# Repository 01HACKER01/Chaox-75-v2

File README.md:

# Chaox-75-v2

## what is this ??
this is a keyboard with tri mode connectivity it can be connected with the dongle(2.4gHZ), bluetooth and wired. it also charges while connected to wired 

## why it exists
i have an old evofox keyboard which is not a good keyboard i cant type fast on that keyboard sometimes the keys doesnt get clicked or sometimes teh key gets stuck so i wanted to buy a keyboard but i thought lets make one by myself so thats why i made this.

## how to assemble 
u can just place all the comps on their places on the pcb and solder them and than flash it.

## firmware stuff
this repo has the code and pcb files for my chaox-75 keyboard. i wrote the firmware in c using zephyr rtos for the nrf52840.

### what it does
* 6x15 key matrix
* works over usb (hid)
* custom fn layer with arrow keys, f-key shortcuts, and media controls

### folders
* `keyboard/` - main firmware code
* `hardware/` - pcb and schematic files
* `dongle/` - 2.4ghz dongle code
* `release/` - precompiled firmware files if u dont wanna build it urself

## how to flash
1. plug the keyboard into your pc with a usb-c cable.
2. double press the reset button on the pcb (or short the rst and gnd pins) to put it into bootloader mode. a new drive should pop up on your pc.
3. grab the `.uf2` firmware file from the releases and just drag and drop it onto that drive.
4. it will disconnect and reboot by itself in a couple seconds and ur good to go.

### what u need to build it
* nrf connect sdk 3.4.1
* zephyr rtos
* cmake & west

### status
still a work in progress (pre-release) so expect some bugs. im still working on it and will push updates when i fix things.
## issues 
it has one issue it doesnt have a switch which can change teh connectivity l;ike the dongle bluetooth or the wired thats an issue which will i fix soon.

---

Made for the CHAOX-75 project.

**CHAOX-75**  
*Custom keyboard firmware, built from the ground up.*

## BOM

| Part | Qty | Approx. USD | Link |
| -------------------------------------- | -- | ------------ | -------------------------------------------------------------------------------------------------------------------------------------------------------------- |
| Custom 82-key Keyboard PCB (5 pcs) | 1 | ~$10–25 | [JLCPCB](https://jlcpcb.com/) |
| 1.5mm Anodized Aluminum Switch Plate | 1 | ~$12–22 | [JLCPCB CNC](https://jlcpcb.com/cnc-machining) |
| 3D Printed Keyboard Case (Top & Bottom) | 1 | ~$10–20 | [JLCPCB 3D Print](https://jlcpcb.com/3d-printing) |
| MX mechanical switches (90 pcs) | 1 | ~$18–35 | [Alibaba MX switches](https://www.alibaba.com/trade/search?SearchText=mechanical+keyboard+switches+90pcs) |
| PBT keycap set (82-key / 75%) | 1 | ~$15–30 | [Alibaba PBT keycaps](https://www.alibaba.com/trade/search?SearchText=PBT+keycaps+set) |
| Kailh MX hotswap sockets (100 pcs) | 1 | ~$6–10 | [LCSC Kailh sockets](https://www.lcsc.com/search?q=kailh%20socket) |
| SK6812MINI-E reverse-mount RGB LEDs (100 pcs) | 1 | ~$8–14 | [LCSC SK6812MINI-E](https://www.lcsc.com/search?q=SK6812MINI-E) |
| 1N4148W SOD-123 diodes (100 pcs) | 1 | ~$1–2 | [LCSC 1N4148W](https://www.lcsc.com/search?q=1N4148W) |
| PCB-mount screw-in stabilizers | 1 | ~$6–12 | [Alibaba PCB stabilizers](https://www.alibaba.com/trade/search?SearchText=PCB+mount+stabilizers) |
| EC11 rotary encoder with metal knob | 1 | ~$1–2 | [LCSC EC11 encoder](https://www.lcsc.com/search?q=EC11%20encoder) |
| 0.91" 128×32 I2C OLED display | 1 | ~$1.50–3 | [LCSC 0.91 OLED](https://www.lcsc.com/search?q=0.91%20inch%20OLED%20I2C) |
| 3.7V 2500–3000mAh LiPo battery (JST-PH 2.0) | 1 | ~$5–9 | [Alibaba LiPo battery](https://www.alibaba.com/trade/search?SearchText=3.7V+3000mAh+lipo+battery+JST) |
| Poron plate foam & switch pads | 1 | ~$3–6 | [Alibaba keyboard poron foam](https://www.alibaba.com/trade/search?SearchText=poron+foam+keyboard) |
| M2 heat-set brass inserts (20 pcs) | 1 | ~$1–3 | [Alibaba M2 heat-set inserts](https://www.alibaba.com/trade/search?SearchText=M2+heat+set+inserts) |
| M2 hex socket screws (20 pcs) | 1 | ~$1–2 | [Alibaba M2 screws](https://www.alibaba.com/trade/search?SearchText=M2+hex+screws) |
| Silicone rubber anti-slip feet (4 pcs) | 1 | ~$0.50–1.50 | [Alibaba silicone bumpons](https://www.alibaba.com/trade/search?SearchText=silicone+bumpons) |
| Braided USB-A → USB-C cable | 1 | ~$2–4 | [Alibaba USB-C cable](https://www.alibaba.com/trade/search?SearchText=braided+usb-c+cable) |
| Custom 2.4GHz USB Dongle (PCB + components) | 1 | ~$8–12 | [JLCPCB](https://jlcpcb.com/) |

### 💰 Estimated total

**Parts: About $110–210 USD**

**Estimated shipping: ~$25–45 USD**

**Total including shipping: About $135–255 USD**, depending heavily on the seller, quantity and shipping.

## Made by Chaox And Arnav
## Thank you very much

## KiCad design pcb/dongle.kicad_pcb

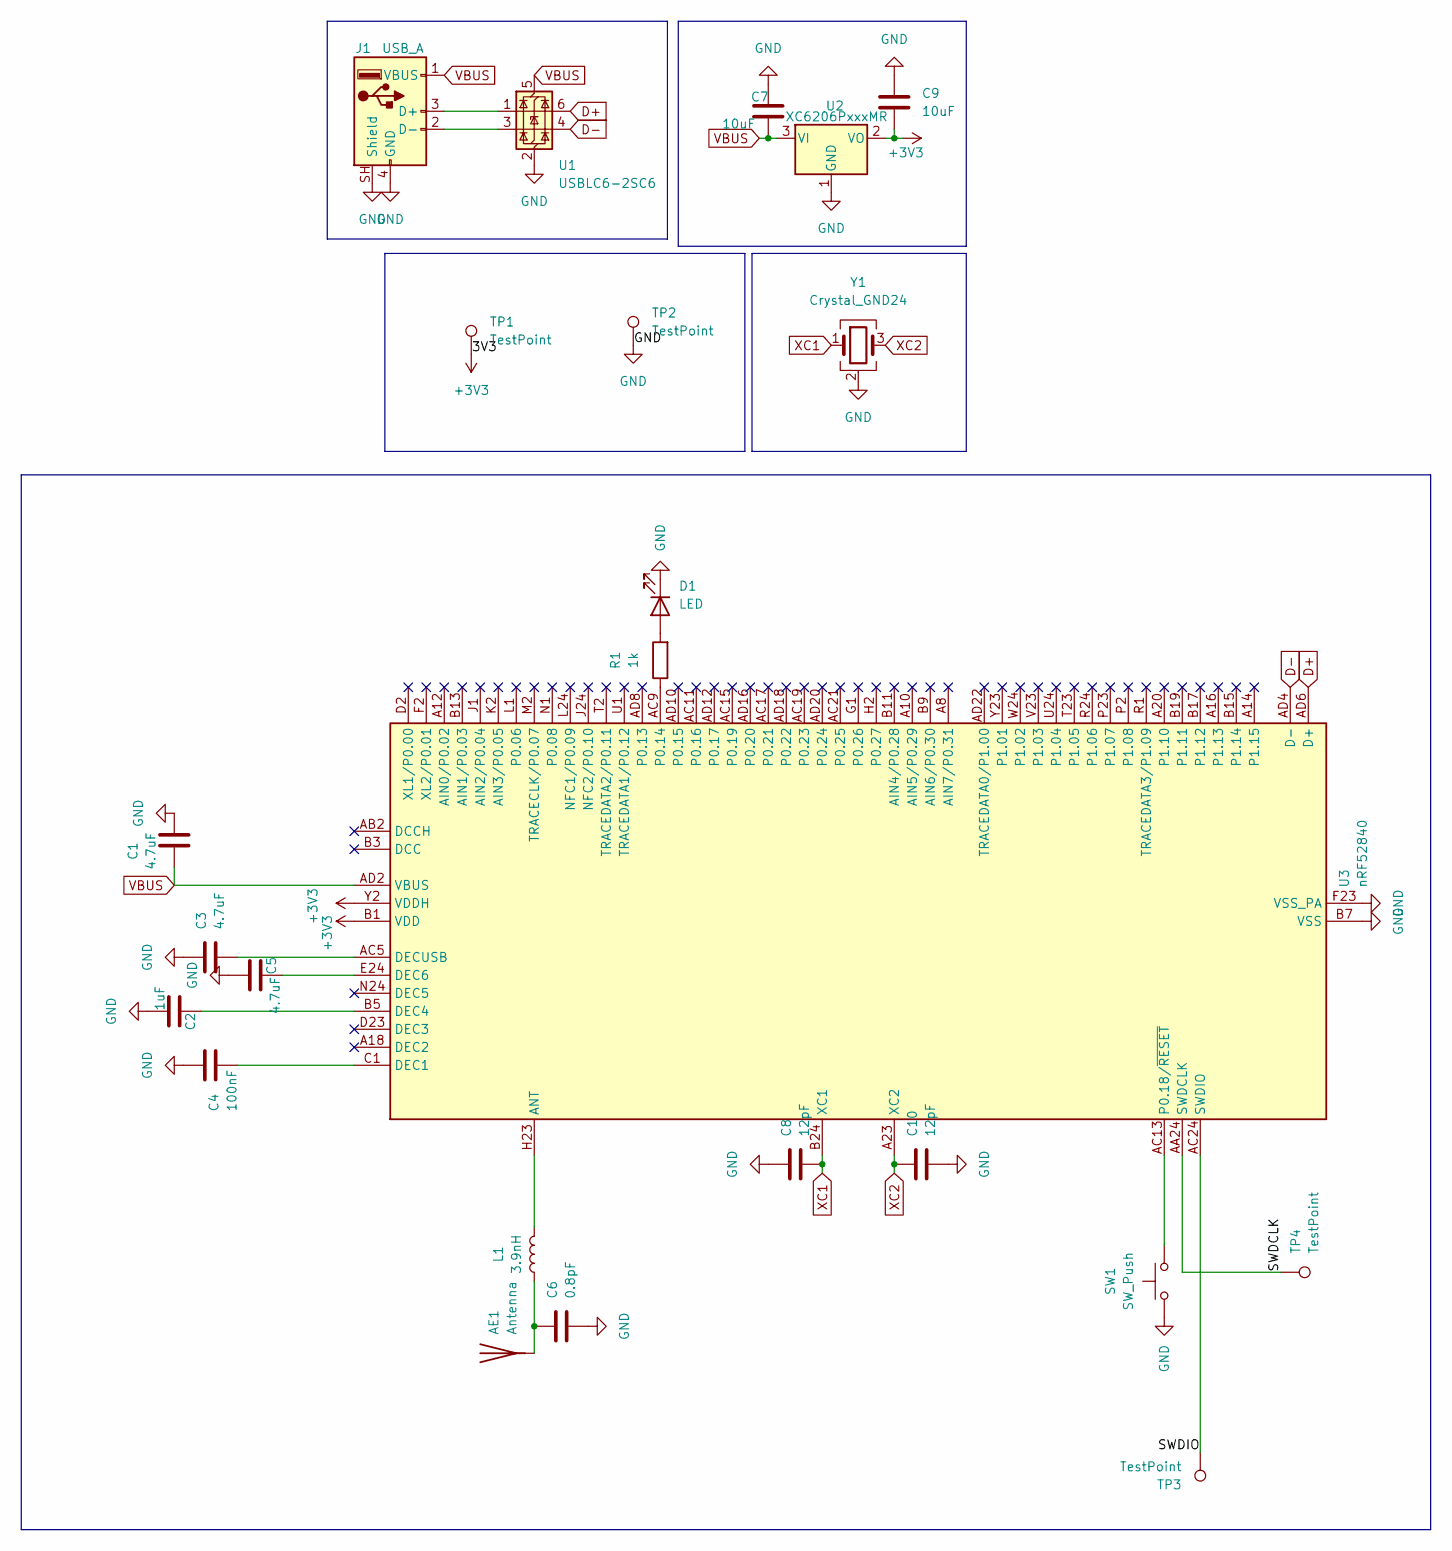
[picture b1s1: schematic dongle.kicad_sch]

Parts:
AE1: Antenna; Texas_SWRA117D_2.4GHz_Left
C1, C3, C5: 4.7uF; C_0603_1608Metric
C2: 1uF; C_0603_1608Metric
C4: 100nF; C_0603_1608Metric
C6: 0.8pF; C_0603_1608Metric
C7, C9: 10uF; C_0603_1608Metric
C8, C10: 12pF; C_0603_1608Metric
D1: LED; LED_0603_1608Metric
J1: USB_A; USB_A_Molex_67643_Horizontal
L1: 3.9nH; L_0603_1608Metric
R1: 1k; R_0603_1608Metric
SW1: SW_Push; SW_Push_1P1T_NO_CK_KMR2
TP1, TP2, TP3, TP4: TestPoint; TestPoint_Pad_D1.0mm
U1: USBLC6-2SC6; SOT-23-6
U2: XC6206PxxxMR; SOT-23-3
U3: nRF52840; Nordic_AQFN-73-1EP_7x7mm_P0.5mm
Y1: Crystal_GND24; Crystal_SMD_3225-4Pin_3.2x2.5mm

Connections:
+3V3: C9.2, TP1.1 (1_1), U2.2 (VO), U3.A22 (VDD), U3.AD14 (VDD), U3.AD23 (VDD), U3.B1 (VDD), U3.W1 (VDD), U3.Y2 (VDDH)
/SWDCLK: TP4.1 (1_1), U3.AA24 (SWDCLK)
/SWDIO: TP3.1 (1_1), U3.AC24 (SWDIO)
D+: U1.6 (I/O1), U3.AD6 (D+)
D-: U1.4 (I/O2), U3.AD4 (D-)
GND: AE1.2, C1.2, C2.1, C3.1, C4.1, C5.1, C6.2, C7.1, C8.1, C9.1, C10.2, D1.1 (K), J1.4 (GND), J1.SH (Shield), SW1.1, TP2.1 (1_1), U1.2 (GND), U2.1 (GND), U3.B7 (VSS), U3.EP (VSS), U3.F23 (VSS_PA), Y1.2 (G), Y1.4 (G)
unnamed: AE1.1 (A_1), C6.1, L1.1
unnamed: D1.2 (A), R1.2
unnamed: J1.3 (D+), U1.1 (I/O1)
unnamed: J1.2 (D-), U1.3 (I/O2)
unnamed: L1.2, U3.H23 (ANT)
unnamed: C4.2, U3.C1 (DEC1)
unnamed: C2.2, U3.B5 (DEC4)
unnamed: C5.2, U3.E24 (DEC6)
unnamed: C3.2, U3.AC5 (DECUSB)
unnamed: R1.1, U3.AC9 (P0.14)
unnamed: SW1.2, U3.AC13 (P0.18/~RESET)
VBUS: C1.1, C7.2, J1.1 (VBUS), U1.5 (VBUS), U2.3 (VI), U3.AD2 (VBUS)
XC1: C8.2, U3.B24 (XC1), Y1.1
XC2: C10.1, U3.A23 (XC2), Y1.3

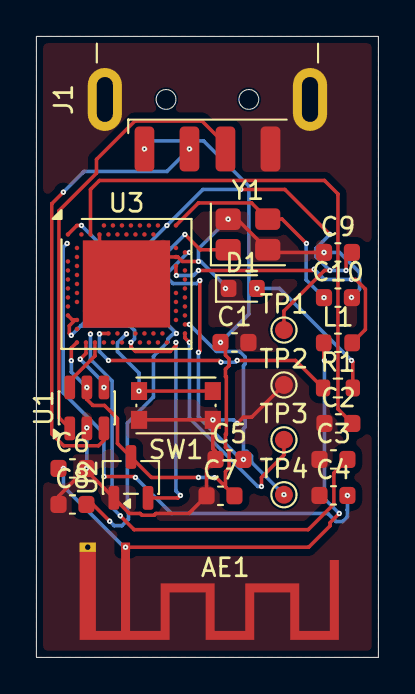
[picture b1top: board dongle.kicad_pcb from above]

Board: 2 copper layers, 19.0 x 34.5 mm, 24 parts (0 on the bottom side), 20 nets.

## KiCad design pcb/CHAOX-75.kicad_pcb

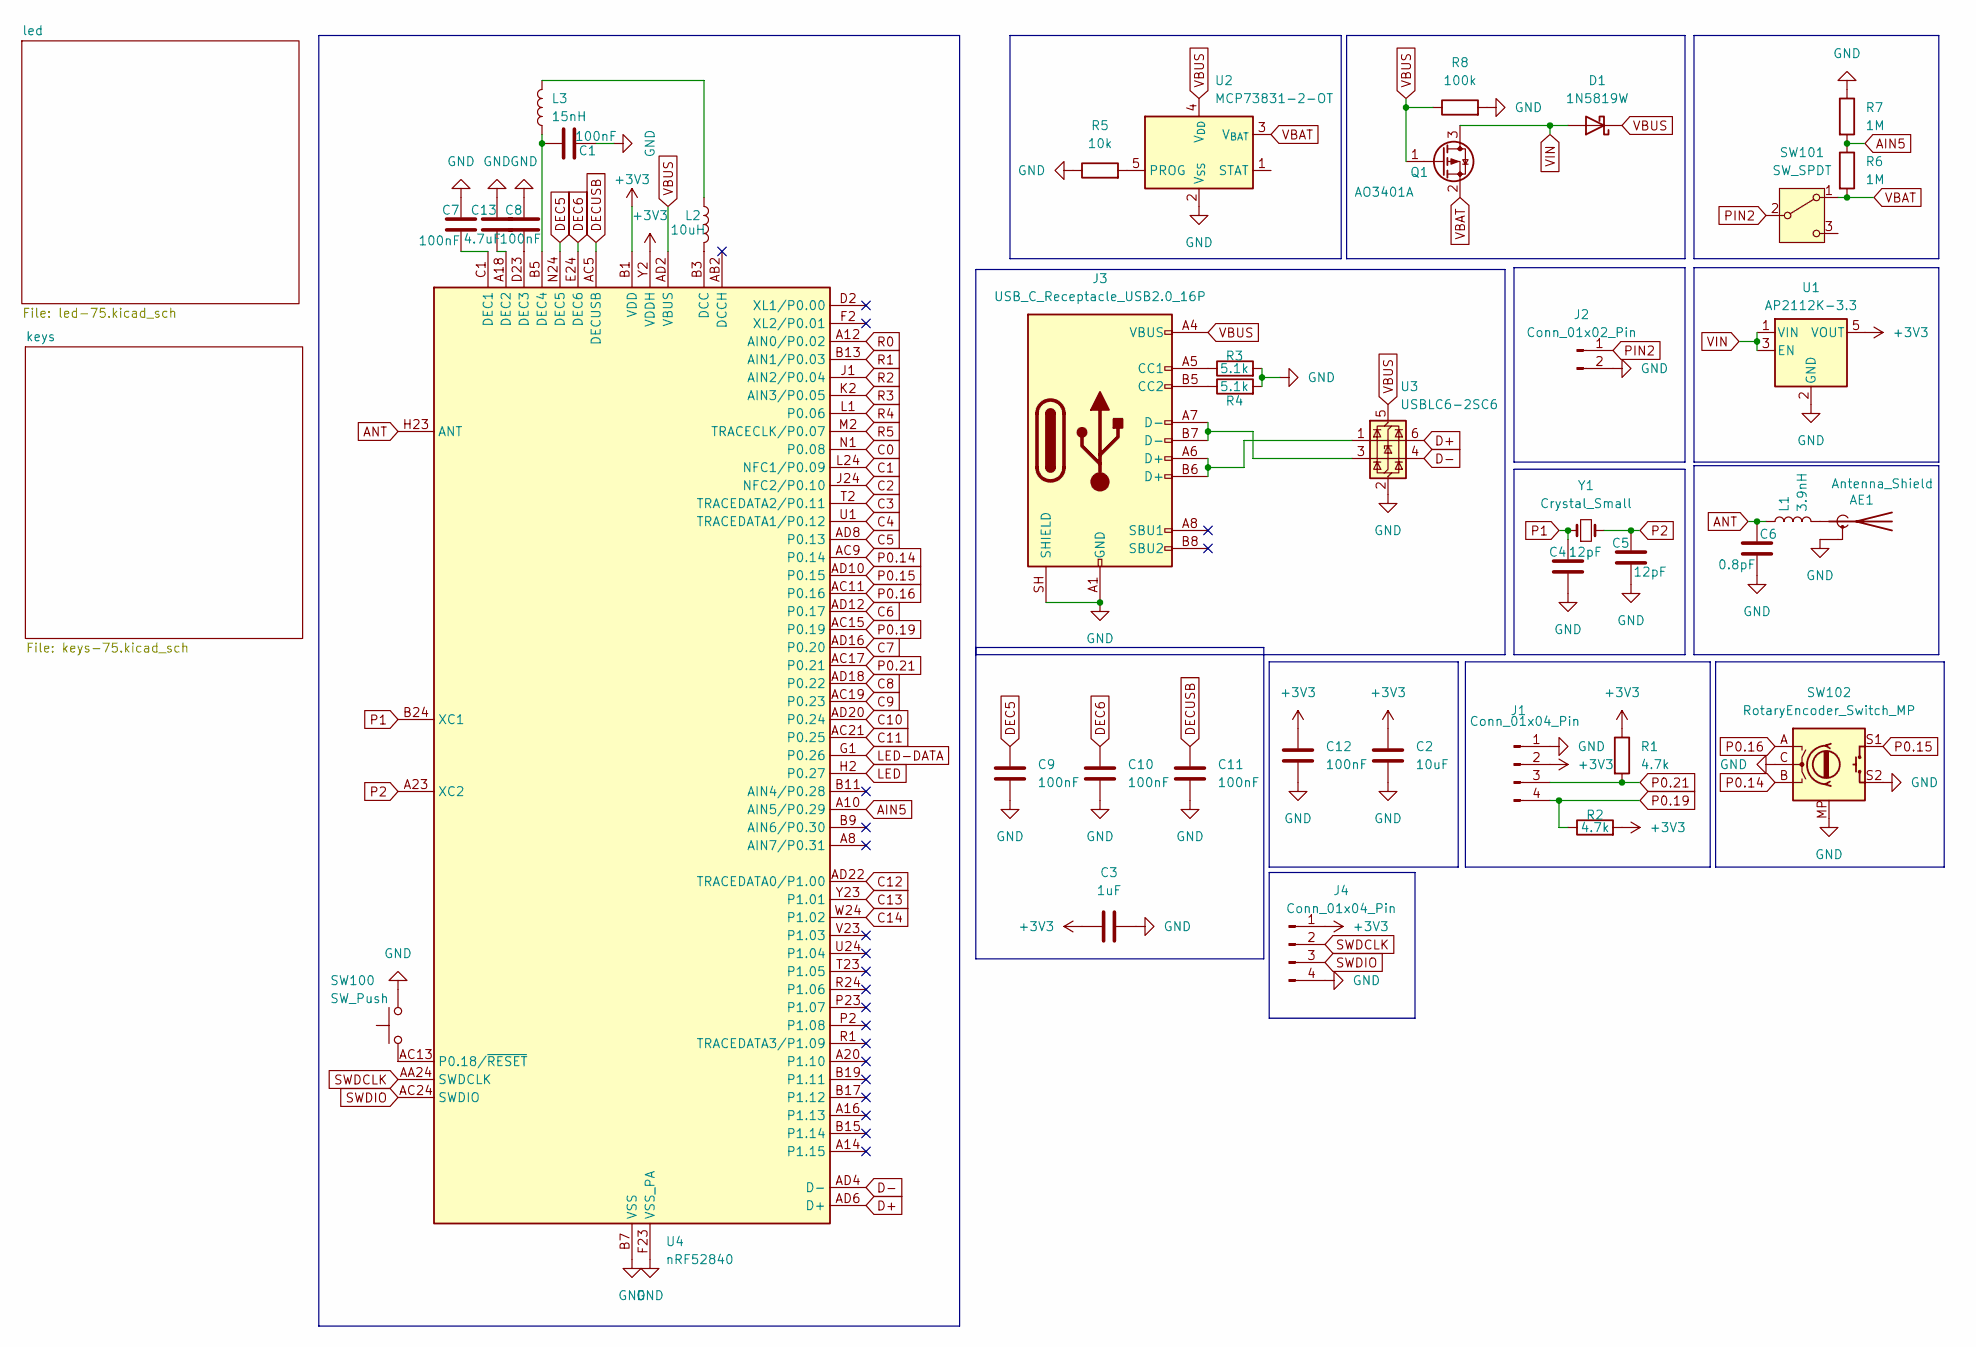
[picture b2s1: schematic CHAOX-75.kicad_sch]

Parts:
AE1: Antenna_Shield; Texas_SWRA117D_2.4GHz_Left
C1, C7, C8, C9, C10, C11, C12: 100nF; C_0603_1608Metric
C2: 10uF; C_0603_1608Metric
C3: 1uF; C_0603_1608Metric
C4, C5: 12pF; C_0603_1608Metric
C6: 0.8pF; C_0603_1608Metric
C13: 4.7uF; C_0603_1608Metric
D1: 1N5819W; D_SOD-123
J1, J4: Conn_01x04_Pin; PinHeader_1x04_P2.54mm_Vertical
J2: Conn_01x02_Pin; PinHeader_1x02_P2.54mm_Vertical
J3: USB_C_Receptacle_USB2.0_16P; USB_C_Receptacle_HRO_TYPE-C-31-M-12
L1: 3.9nH; L_0603_1608Metric
L2: 10uH; L_0603_1608Metric
L3: 15nH; L_0603_1608Metric
Q1: AO3401A; SOT-23
R1, R2: 4.7k; R_0603_1608Metric
R3, R4: 5.1k; R_0603_1608Metric
R5: 10k; R_0603_1608Metric
R6, R7: 1M; R_0603_1608Metric
R8: 100k; R_0603_1608Metric
SW100: SW_Push; SW_Tactile_SPST_NO_Straight_CK_PTS636Sx25SMTRLFS
SW101: SW_SPDT; SW_Slide_SPDT_Straight_CK_OS102011MS2Q
SW102: RotaryEncoder_Switch_MP; RotaryEncoder_Alps_EC11E-Switch_Vertical_H20mm
U1: AP2112K-3.3; SOT-23-5
U2: MCP73831-2-OT; SOT-23-5
U3: USBLC6-2SC6; SOT-23-6
U4: nRF52840; Nordic_AQFN-73-1EP_7x7mm_P0.5mm
Y1: Crystal_Small; Crystal_SMD_3225-4Pin_3.2x2.5mm

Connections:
+3V3: C2.1, C3.1, C12.1, J1.2, J4.1, R1.1, R2.2, U1.5 (VOUT), U4.A22 (VDD), U4.AD14 (VDD), U4.AD23 (VDD), U4.B1 (VDD), U4.W1 (VDD), U4.Y2 (VDDH)
AIN5: R6.1, R7.2, U4.A10 (AIN5/P0.29)
ANT: C6.1, L1.1, U4.H23 (ANT)
C0: U4.N1 (P0.08); also elsewhere on the board
C1: U4.L24 (NFC1/P0.09); also elsewhere on the board
C2: U4.J24 (NFC2/P0.10); also elsewhere on the board
C3: U4.T2 (TRACEDATA2/P0.11); also elsewhere on the board
C4: U4.U1 (TRACEDATA1/P0.12); also elsewhere on the board
C5: U4.AD8 (P0.13); also elsewhere on the board
C6: U4.AD12 (P0.17); also elsewhere on the board
C7: U4.AD16 (P0.20); also elsewhere on the board
C8: U4.AD18 (P0.22); also elsewhere on the board
C9: U4.AC19 (P0.23); also elsewhere on the board
C10: U4.AD20 (P0.24); also elsewhere on the board
C11: U4.AC21 (P0.25); also elsewhere on the board
C12: U4.AD22 (TRACEDATA0/P1.00); also elsewhere on the board
C13: U4.Y23 (P1.01); also elsewhere on the board
C14: U4.W24 (P1.02); also elsewhere on the board
D+: U3.6 (I/O1), U4.AD6 (D+)
D-: U3.4 (I/O2), U4.AD4 (D-)
DEC5: C9.1, U4.N24 (DEC5)
DEC6: C10.1, U4.E24 (DEC6)
DECUSB: C11.1, U4.AC5 (DECUSB)
GND: AE1.2 (Shield), C1.1, C2.2, C3.2, C4.2, C5.2, C6.2, C7.1, C8.1, C9.2, C10.2, C11.2, C12.2, C13.1, J1.1, J2.2, J3.A1 (GND), J3.A12 (GND), J3.B1 (GND), J3.B12 (GND), J3.SH (SHIELD), J4.4, R3.2, R4.2, R5.1, R7.1, R8.2, SW100.2, SW102.C, SW102.MP, SW102.S2, U1.2 (GND), U2.2 (V_{SS}), U3.2 (GND), U4.B7 (VSS), U4.EP (VSS), U4.F23 (VSS_PA); also elsewhere on the board
LED: U4.H2 (P0.27); also elsewhere on the board
LED-DATA: U4.G1 (P0.26); also elsewhere on the board
unnamed: AE1.1 (A), L1.2
unnamed: J3.A5 (CC1), R3.1
unnamed: J3.B5 (CC2), R4.1
unnamed: J3.A6 (D+), J3.B6 (D+), U3.1 (I/O1)
unnamed: J3.A7 (D-), J3.B7 (D-), U3.3 (I/O2)
unnamed: L2.1, L3.2
unnamed: R5.2, U2.5 (PROG)
unnamed: L2.2, U4.B3 (DCC)
unnamed: C7.2, U4.C1 (DEC1)
unnamed: C13.2, U4.A18 (DEC2)
unnamed: C8.2, U4.D23 (DEC3)
unnamed: C1.2, L3.1, U4.B5 (DEC4)
unnamed: SW100.1, U4.AC13 (P0.18/~RESET)
P0.14: SW102.B, U4.AC9 (P0.14)
P0.15: SW102.S1, U4.AD10 (P0.15)
P0.16: SW102.A, U4.AC11 (P0.16)
P0.19: J1.4, R2.1, U4.AC15 (P0.19)
P0.21: J1.3, R1.2, U4.AC17 (P0.21)
P1: C4.1, U4.B24 (XC1), Y1.1
P2: C5.1, U4.A23 (XC2), Y1.2
PIN2: J2.1, SW101.2 (B)
R0: U4.A12 (AIN0/P0.02); also elsewhere on the board
R1: U4.B13 (AIN1/P0.03); also elsewhere on the board
R2: U4.J1 (AIN2/P0.04); also elsewhere on the board
R3: U4.K2 (AIN3/P0.05); also elsewhere on the board
R4: U4.L1 (P0.06); also elsewhere on the board
R5: U4.M2 (TRACECLK/P0.07); also elsewhere on the board
SWDCLK: J4.2, U4.AA24 (SWDCLK)
SWDIO: J4.3, U4.AC24 (SWDIO)
VBAT: Q1.2 (S), R6.2, SW101.1 (A), U2.3 (V_{BAT}); also elsewhere on the board
VBUS: D1.1 (K), J3.A4 (VBUS), J3.A9 (VBUS), J3.B4 (VBUS), J3.B9 (VBUS), Q1.1 (G), R8.1, U2.4 (V_{DD}), U3.5 (VBUS), U4.AD2 (VBUS)
VIN: D1.2 (A), Q1.3 (D), U1.1 (VIN), U1.3 (EN)

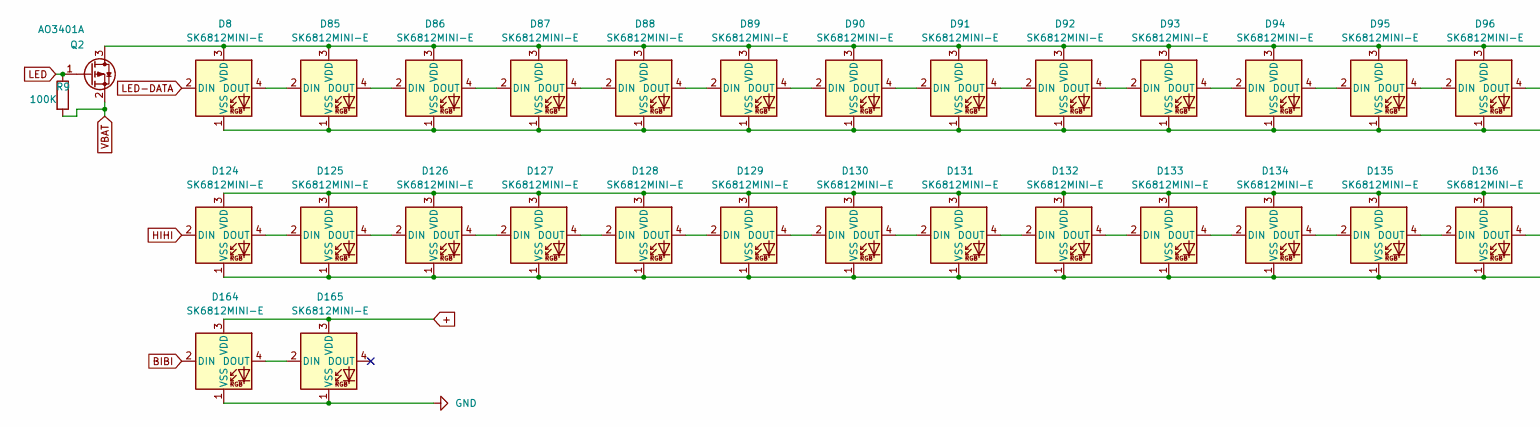
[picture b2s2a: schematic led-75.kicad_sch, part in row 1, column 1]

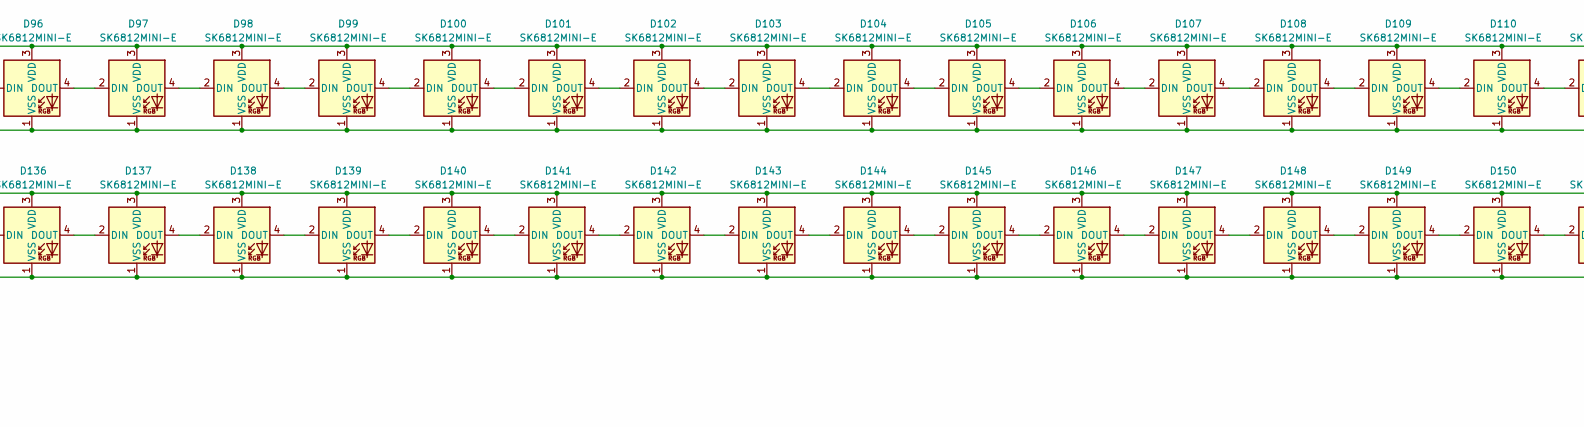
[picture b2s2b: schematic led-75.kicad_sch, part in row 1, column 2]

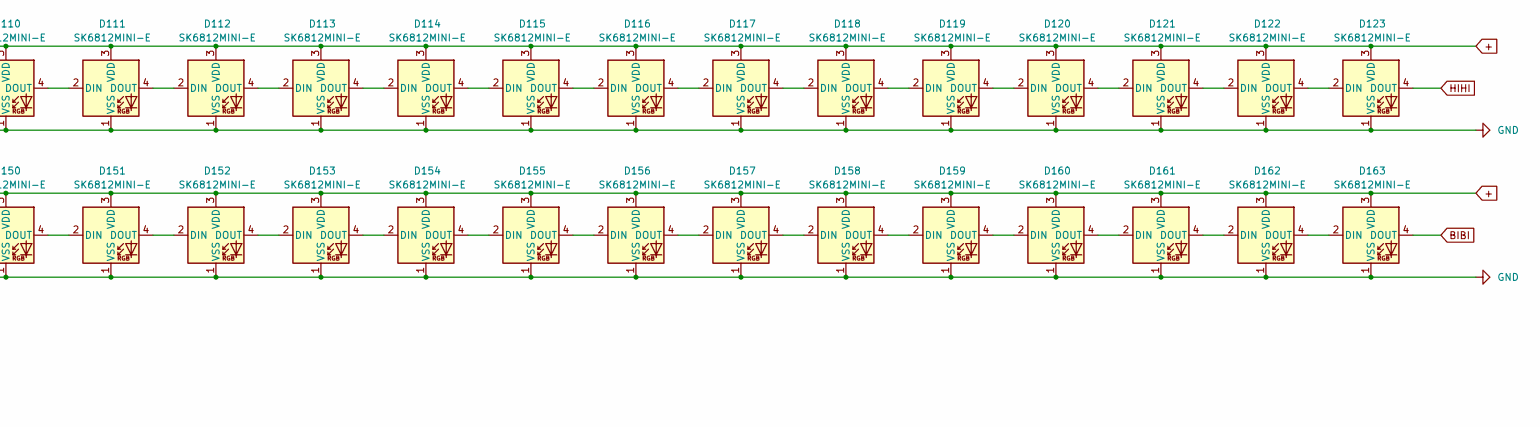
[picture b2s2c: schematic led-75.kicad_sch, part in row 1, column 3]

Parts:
D8, D85, D86, D87, D88, D89, D90, D91, D92, D93, D94, D95, D96, D97, D98, D99, D100, D101, D102, D103, D104, D105, D106, D107, D108, D109, D110, D111, D112, D113, D114, D115, D116, D117, D118, D119, D120, D121, D122, D123, D124, D125, D126, D127, D128, D129, D130, D131, D132, D133, D134, D135, D136, D137, D138, D139, D140, D141, D142, D143, D144, D145, D146, D147, D148, D149, D150, D151, D152, D153, D154, D155, D156, D157, D158, D159, D160, D161, D162, D163, D164, D165: SK6812MINI-E; MX_SK6812MINI-E
Q2: AO3401A; SOT-23
R9: 100K; R_0603_1608Metric

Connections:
+: D8.3 (VDD), D85.3 (VDD), D86.3 (VDD), D87.3 (VDD), D88.3 (VDD), D89.3 (VDD), D90.3 (VDD), D91.3 (VDD), D92.3 (VDD), D93.3 (VDD), D94.3 (VDD), D95.3 (VDD), D96.3 (VDD), D97.3 (VDD), D98.3 (VDD), D99.3 (VDD), D100.3 (VDD), D101.3 (VDD), D102.3 (VDD), D103.3 (VDD), D104.3 (VDD), D105.3 (VDD), D106.3 (VDD), D107.3 (VDD), D108.3 (VDD), D109.3 (VDD), D110.3 (VDD), D111.3 (VDD), D112.3 (VDD), D113.3 (VDD), D114.3 (VDD), D115.3 (VDD), D116.3 (VDD), D117.3 (VDD), D118.3 (VDD), D119.3 (VDD), D120.3 (VDD), D121.3 (VDD), D122.3 (VDD), D123.3 (VDD), D124.3 (VDD), D125.3 (VDD), D126.3 (VDD), D127.3 (VDD), D128.3 (VDD), D129.3 (VDD), D130.3 (VDD), D131.3 (VDD), D132.3 (VDD), D133.3 (VDD), D134.3 (VDD), D135.3 (VDD), D136.3 (VDD), D137.3 (VDD), D138.3 (VDD), D139.3 (VDD), D140.3 (VDD), D141.3 (VDD), D142.3 (VDD), D143.3 (VDD), D144.3 (VDD), D145.3 (VDD), D146.3 (VDD), D147.3 (VDD), D148.3 (VDD), D149.3 (VDD), D150.3 (VDD), D151.3 (VDD), D152.3 (VDD), D153.3 (VDD), D154.3 (VDD), D155.3 (VDD), D156.3 (VDD), D157.3 (VDD), D158.3 (VDD), D159.3 (VDD), D160.3 (VDD), D161.3 (VDD), D162.3 (VDD), D163.3 (VDD), D164.3 (VDD), D165.3 (VDD), Q2.3 (D)
BIBI: D163.4 (DOUT), D164.2 (DIN)
GND: D8.1 (VSS), D85.1 (VSS), D86.1 (VSS), D87.1 (VSS), D88.1 (VSS), D89.1 (VSS), D90.1 (VSS), D91.1 (VSS), D92.1 (VSS), D93.1 (VSS), D94.1 (VSS), D95.1 (VSS), D96.1 (VSS), D97.1 (VSS), D98.1 (VSS), D99.1 (VSS), D100.1 (VSS), D101.1 (VSS), D102.1 (VSS), D103.1 (VSS), D104.1 (VSS), D105.1 (VSS), D106.1 (VSS), D107.1 (VSS), D108.1 (VSS), D109.1 (VSS), D110.1 (VSS), D111.1 (VSS), D112.1 (VSS), D113.1 (VSS), D114.1 (VSS), D115.1 (VSS), D116.1 (VSS), D117.1 (VSS), D118.1 (VSS), D119.1 (VSS), D120.1 (VSS), D121.1 (VSS), D122.1 (VSS), D123.1 (VSS), D124.1 (VSS), D125.1 (VSS), D126.1 (VSS), D127.1 (VSS), D128.1 (VSS), D129.1 (VSS), D130.1 (VSS), D131.1 (VSS), D132.1 (VSS), D133.1 (VSS), D134.1 (VSS), D135.1 (VSS), D136.1 (VSS), D137.1 (VSS), D138.1 (VSS), D139.1 (VSS), D140.1 (VSS), D141.1 (VSS), D142.1 (VSS), D143.1 (VSS), D144.1 (VSS), D145.1 (VSS), D146.1 (VSS), D147.1 (VSS), D148.1 (VSS), D149.1 (VSS), D150.1 (VSS), D151.1 (VSS), D152.1 (VSS), D153.1 (VSS), D154.1 (VSS), D155.1 (VSS), D156.1 (VSS), D157.1 (VSS), D158.1 (VSS), D159.1 (VSS), D160.1 (VSS), D161.1 (VSS), D162.1 (VSS), D163.1 (VSS), D164.1 (VSS), D165.1 (VSS); also elsewhere on the board
HIHI: D123.4 (DOUT), D124.2 (DIN)
LED: Q2.1 (G), R9.1; also elsewhere on the board
LED-DATA: D8.2 (DIN); also elsewhere on the board
unnamed: D8.4 (DOUT), D85.2 (DIN)
unnamed: D85.4 (DOUT), D86.2 (DIN)
unnamed: D86.4 (DOUT), D87.2 (DIN)
unnamed: D87.4 (DOUT), D88.2 (DIN)
unnamed: D88.4 (DOUT), D89.2 (DIN)
unnamed: D89.4 (DOUT), D90.2 (DIN)
unnamed: D90.4 (DOUT), D91.2 (DIN)
unnamed: D91.4 (DOUT), D92.2 (DIN)
unnamed: D92.4 (DOUT), D93.2 (DIN)
unnamed: D93.4 (DOUT), D94.2 (DIN)
unnamed: D94.4 (DOUT), D95.2 (DIN)
unnamed: D95.4 (DOUT), D96.2 (DIN)
unnamed: D96.4 (DOUT), D97.2 (DIN)
unnamed: D97.4 (DOUT), D98.2 (DIN)
unnamed: D98.4 (DOUT), D99.2 (DIN)
unnamed: D99.4 (DOUT), D100.2 (DIN)
unnamed: D100.4 (DOUT), D101.2 (DIN)
unnamed: D101.4 (DOUT), D102.2 (DIN)
unnamed: D102.4 (DOUT), D103.2 (DIN)
unnamed: D103.4 (DOUT), D104.2 (DIN)
unnamed: D104.4 (DOUT), D105.2 (DIN)
unnamed: D105.4 (DOUT), D106.2 (DIN)
unnamed: D106.4 (DOUT), D107.2 (DIN)
unnamed: D107.4 (DOUT), D108.2 (DIN)
unnamed: D108.4 (DOUT), D109.2 (DIN)
unnamed: D109.4 (DOUT), D110.2 (DIN)
unnamed: D110.4 (DOUT), D111.2 (DIN)
unnamed: D111.4 (DOUT), D112.2 (DIN)
unnamed: D112.4 (DOUT), D113.2 (DIN)
unnamed: D113.4 (DOUT), D114.2 (DIN)
unnamed: D114.4 (DOUT), D115.2 (DIN)
unnamed: D115.4 (DOUT), D116.2 (DIN)
unnamed: D116.4 (DOUT), D117.2 (DIN)
unnamed: D117.4 (DOUT), D118.2 (DIN)
unnamed: D118.4 (DOUT), D119.2 (DIN)
unnamed: D119.4 (DOUT), D120.2 (DIN)
unnamed: D120.4 (DOUT), D121.2 (DIN)
unnamed: D121.4 (DOUT), D122.2 (DIN)
unnamed: D122.4 (DOUT), D123.2 (DIN)
unnamed: D124.4 (DOUT), D125.2 (DIN)
unnamed: D125.4 (DOUT), D126.2 (DIN)
unnamed: D126.4 (DOUT), D127.2 (DIN)
unnamed: D127.4 (DOUT), D128.2 (DIN)
unnamed: D128.4 (DOUT), D129.2 (DIN)
unnamed: D129.4 (DOUT), D130.2 (DIN)
unnamed: D130.4 (DOUT), D131.2 (DIN)
unnamed: D131.4 (DOUT), D132.2 (DIN)
unnamed: D132.4 (DOUT), D133.2 (DIN)
unnamed: D133.4 (DOUT), D134.2 (DIN)
unnamed: D134.4 (DOUT), D135.2 (DIN)
unnamed: D135.4 (DOUT), D136.2 (DIN)
unnamed: D136.4 (DOUT), D137.2 (DIN)
unnamed: D137.4 (DOUT), D138.2 (DIN)
unnamed: D138.4 (DOUT), D139.2 (DIN)
unnamed: D139.4 (DOUT), D140.2 (DIN)
unnamed: D140.4 (DOUT), D141.2 (DIN)
unnamed: D141.4 (DOUT), D142.2 (DIN)
unnamed: D142.4 (DOUT), D143.2 (DIN)
unnamed: D143.4 (DOUT), D144.2 (DIN)
unnamed: D144.4 (DOUT), D145.2 (DIN)
unnamed: D145.4 (DOUT), D146.2 (DIN)
unnamed: D146.4 (DOUT), D147.2 (DIN)
unnamed: D147.4 (DOUT), D148.2 (DIN)
unnamed: D148.4 (DOUT), D149.2 (DIN)
unnamed: D149.4 (DOUT), D150.2 (DIN)
unnamed: D150.4 (DOUT), D151.2 (DIN)
unnamed: D151.4 (DOUT), D152.2 (DIN)
unnamed: D152.4 (DOUT), D153.2 (DIN)
unnamed: D153.4 (DOUT), D154.2 (DIN)
unnamed: D154.4 (DOUT), D155.2 (DIN)
unnamed: D155.4 (DOUT), D156.2 (DIN)
unnamed: D156.4 (DOUT), D157.2 (DIN)
unnamed: D157.4 (DOUT), D158.2 (DIN)
unnamed: D158.4 (DOUT), D159.2 (DIN)
unnamed: D159.4 (DOUT), D160.2 (DIN)
unnamed: D160.4 (DOUT), D161.2 (DIN)
unnamed: D161.4 (DOUT), D162.2 (DIN)
unnamed: D162.4 (DOUT), D163.2 (DIN)
unnamed: D164.4 (DOUT), D165.2 (DIN)
VBAT: Q2.2 (S), R9.2; also elsewhere on the board

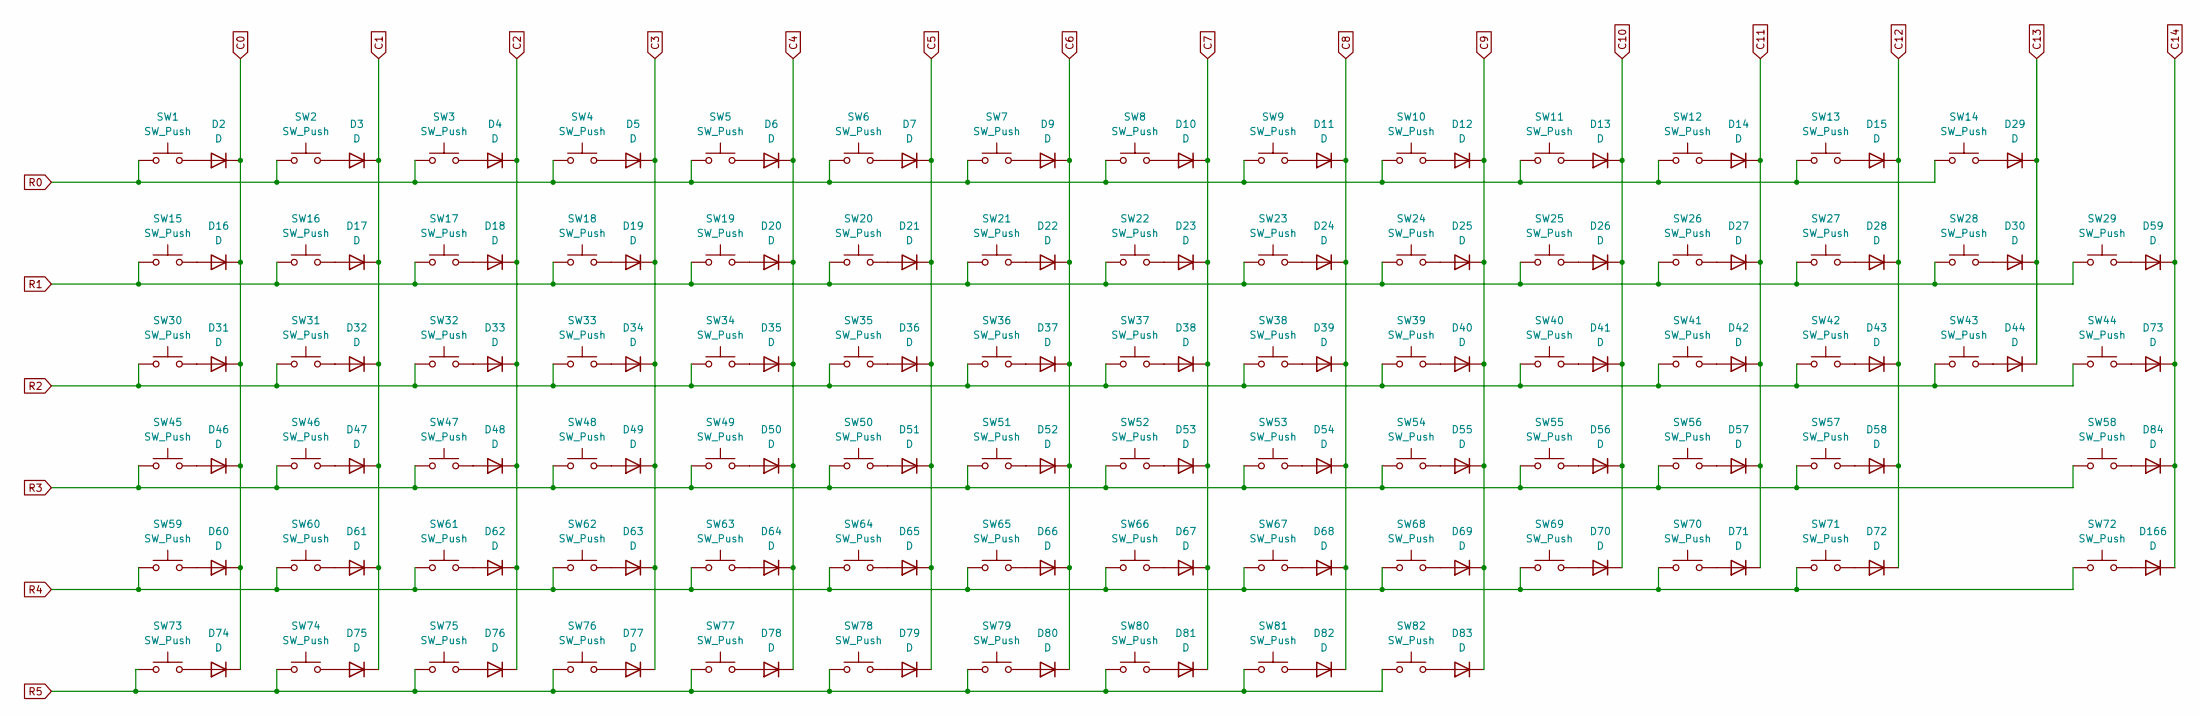
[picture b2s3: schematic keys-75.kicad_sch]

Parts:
D2, D3, D4, D5, D6, D7, D9, D10, D11, D12, D13, D14, D15, D16, D17, D18, D19, D20, D21, D22, D23, D24, D25, D26, D27, D28, D29, D30, D31, D32, D33, D34, D35, D36, D37, D38, D39, D40, D41, D42, D43, D44, D46, D47, D48, D49, D50, D51, D52, D53, D54, D55, D56, D57, D58, D59, D60, D61, D62, D63, D64, D65, D66, D67, D68, D69, D70, D71, D72, D73, D74, D75, D76, D77, D78, D79, D80, D81, D82, D83, D84, D166: D; D_SOD-123
SW1, SW2, SW3, SW4, SW5, SW6, SW7, SW8, SW9, SW10, SW11, SW12, SW13, SW14, SW15, SW16, SW17, SW18, SW19, SW20, SW21, SW22, SW23, SW24, SW25, SW26, SW27, SW28, SW29, SW30, SW31, SW32, SW33, SW34, SW35, SW36, SW37, SW38, SW39, SW40, SW41, SW42, SW43, SW44, SW45, SW46, SW47, SW48, SW49, SW50, SW51, SW52, SW53, SW54, SW55, SW56, SW57, SW58, SW59, SW60, SW61, SW62, SW63, SW64, SW65, SW66, SW67, SW68, SW69, SW70, SW71, SW72, SW73, SW74, SW75, SW76, SW77, SW78, SW79, SW80, SW81, SW82: SW_Push; SW_Hotswap_Kailh_MX_1.00u

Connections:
C0: D2.1 (K), D16.1 (K), D31.1 (K), D46.1 (K), D60.1 (K), D74.1 (K); also elsewhere on the board
C1: D3.1 (K), D17.1 (K), D32.1 (K), D47.1 (K), D61.1 (K), D75.1 (K); also elsewhere on the board
C2: D4.1 (K), D18.1 (K), D33.1 (K), D48.1 (K), D62.1 (K), D76.1 (K); also elsewhere on the board
C3: D5.1 (K), D19.1 (K), D34.1 (K), D49.1 (K), D63.1 (K), D77.1 (K); also elsewhere on the board
C4: D6.1 (K), D20.1 (K), D35.1 (K), D50.1 (K), D64.1 (K), D78.1 (K); also elsewhere on the board
C5: D7.1 (K), D21.1 (K), D36.1 (K), D51.1 (K), D65.1 (K), D79.1 (K); also elsewhere on the board
C6: D9.1 (K), D22.1 (K), D37.1 (K), D52.1 (K), D66.1 (K), D80.1 (K); also elsewhere on the board
C7: D10.1 (K), D23.1 (K), D38.1 (K), D53.1 (K), D67.1 (K), D81.1 (K); also elsewhere on the board
C8: D11.1 (K), D24.1 (K), D39.1 (K), D54.1 (K), D68.1 (K), D82.1 (K); also elsewhere on the board
C9: D12.1 (K), D25.1 (K), D40.1 (K), D55.1 (K), D69.1 (K), D83.1 (K); also elsewhere on the board
C10: D13.1 (K), D26.1 (K), D41.1 (K), D56.1 (K), D70.1 (K); also elsewhere on the board
C11: D14.1 (K), D27.1 (K), D42.1 (K), D57.1 (K), D71.1 (K); also elsewhere on the board
C12: D15.1 (K), D28.1 (K), D43.1 (K), D58.1 (K), D72.1 (K); also elsewhere on the board
C13: D29.1 (K), D30.1 (K), D44.1 (K); also elsewhere on the board
C14: D59.1 (K), D73.1 (K), D84.1 (K), D166.1 (K); also elsewhere on the board
unnamed: D2.2 (A), SW1.2
unnamed: D3.2 (A), SW2.2
unnamed: D4.2 (A), SW3.2
unnamed: D5.2 (A), SW4.2
unnamed: D6.2 (A), SW5.2
unnamed: D7.2 (A), SW6.2
unnamed: D9.2 (A), SW7.2
unnamed: D10.2 (A), SW8.2
unnamed: D11.2 (A), SW9.2
unnamed: D12.2 (A), SW10.2
unnamed: D13.2 (A), SW11.2
unnamed: D14.2 (A), SW12.2
unnamed: D15.2 (A), SW13.2
unnamed: D16.2 (A), SW15.2
unnamed: D17.2 (A), SW16.2
unnamed: D18.2 (A), SW17.2
unnamed: D19.2 (A), SW18.2
unnamed: D20.2 (A), SW19.2
unnamed: D21.2 (A), SW20.2
unnamed: D22.2 (A), SW21.2
unnamed: D23.2 (A), SW22.2
unnamed: D24.2 (A), SW23.2
unnamed: D25.2 (A), SW24.2
unnamed: D26.2 (A), SW25.2
unnamed: D27.2 (A), SW26.2
unnamed: D28.2 (A), SW27.2
unnamed: D29.2 (A), SW14.2
unnamed: D30.2 (A), SW28.2
unnamed: D31.2 (A), SW30.2
unnamed: D32.2 (A), SW31.2
unnamed: D33.2 (A), SW32.2
unnamed: D34.2 (A), SW33.2
unnamed: D35.2 (A), SW34.2
unnamed: D36.2 (A), SW35.2
unnamed: D37.2 (A), SW36.2
unnamed: D38.2 (A), SW37.2
unnamed: D39.2 (A), SW38.2
unnamed: D40.2 (A), SW39.2
unnamed: D41.2 (A), SW40.2
unnamed: D42.2 (A), SW41.2
unnamed: D43.2 (A), SW42.2
unnamed: D44.2 (A), SW43.2
unnamed: D46.2 (A), SW45.2
unnamed: D47.2 (A), SW46.2
unnamed: D48.2 (A), SW47.2
unnamed: D49.2 (A), SW48.2
unnamed: D50.2 (A), SW49.2
unnamed: D51.2 (A), SW50.2
unnamed: D52.2 (A), SW51.2
unnamed: D53.2 (A), SW52.2
unnamed: D54.2 (A), SW53.2
unnamed: D55.2 (A), SW54.2
unnamed: D56.2 (A), SW55.2
unnamed: D57.2 (A), SW56.2
unnamed: D58.2 (A), SW57.2
unnamed: D59.2 (A), SW29.2
unnamed: D60.2 (A), SW59.2
unnamed: D61.2 (A), SW60.2
unnamed: D62.2 (A), SW61.2
unnamed: D63.2 (A), SW62.2
unnamed: D64.2 (A), SW63.2
unnamed: D65.2 (A), SW64.2
unnamed: D66.2 (A), SW65.2
unnamed: D67.2 (A), SW66.2
unnamed: D68.2 (A), SW67.2
unnamed: D69.2 (A), SW68.2
unnamed: D70.2 (A), SW69.2
unnamed: D71.2 (A), SW70.2
unnamed: D72.2 (A), SW71.2
unnamed: D73.2 (A), SW44.2
unnamed: D74.2 (A), SW73.2
unnamed: D75.2 (A), SW74.2
unnamed: D76.2 (A), SW75.2
unnamed: D77.2 (A), SW76.2
unnamed: D78.2 (A), SW77.2
unnamed: D79.2 (A), SW78.2
unnamed: D80.2 (A), SW79.2
unnamed: D81.2 (A), SW80.2
unnamed: D82.2 (A), SW81.2
unnamed: D83.2 (A), SW82.2
unnamed: D84.2 (A), SW58.2
unnamed: D166.2 (A), SW72.2
R0: SW1.1, SW2.1, SW3.1, SW4.1, SW5.1, SW6.1, SW7.1, SW8.1, SW9.1, SW10.1, SW11.1, SW12.1, SW13.1, SW14.1; also elsewhere on the board
R1: SW15.1, SW16.1, SW17.1, SW18.1, SW19.1, SW20.1, SW21.1, SW22.1, SW23.1, SW24.1, SW25.1, SW26.1, SW27.1, SW28.1, SW29.1; also elsewhere on the board
R2: SW30.1, SW31.1, SW32.1, SW33.1, SW34.1, SW35.1, SW36.1, SW37.1, SW38.1, SW39.1, SW40.1, SW41.1, SW42.1, SW43.1, SW44.1; also elsewhere on the board
R3: SW45.1, SW46.1, SW47.1, SW48.1, SW49.1, SW50.1, SW51.1, SW52.1, SW53.1, SW54.1, SW55.1, SW56.1, SW57.1, SW58.1; also elsewhere on the board
R4: SW59.1, SW60.1, SW61.1, SW62.1, SW63.1, SW64.1, SW65.1, SW66.1, SW67.1, SW68.1, SW69.1, SW70.1, SW71.1, SW72.1; also elsewhere on the board
R5: SW73.1, SW74.1, SW75.1, SW76.1, SW77.1, SW78.1, SW79.1, SW80.1, SW81.1, SW82.1; also elsewhere on the board

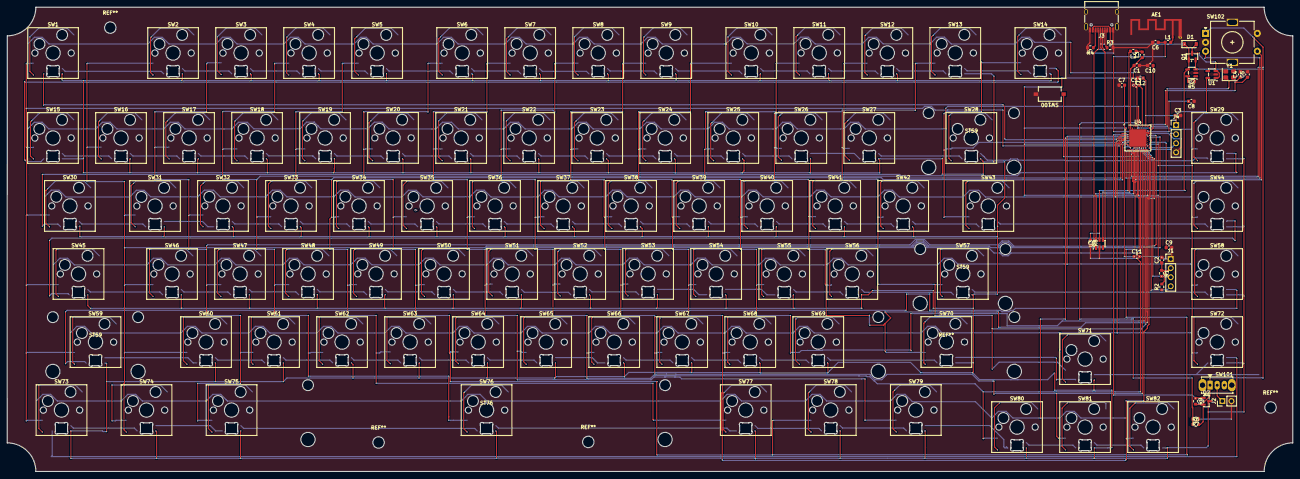
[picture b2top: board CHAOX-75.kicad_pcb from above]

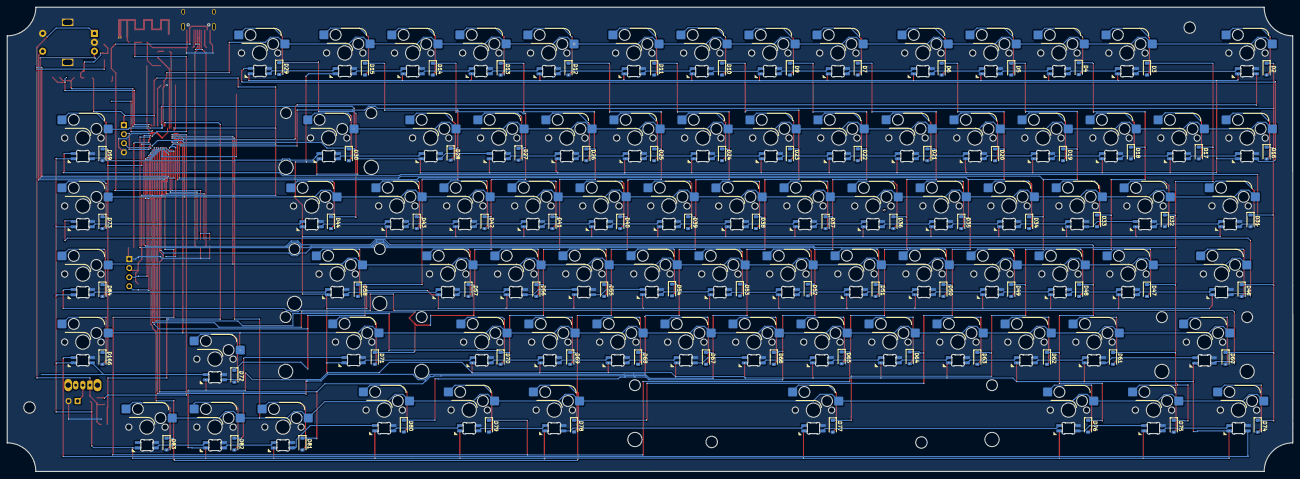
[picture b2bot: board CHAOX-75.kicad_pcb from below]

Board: 2 copper layers, 360.0 x 130.0 mm, 291 parts (82 on the bottom side), 222 nets.

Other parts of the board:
ST59, ST59#2, ST59#3: MountingHole; Stabilizer_Cherry_MX_2.00u
ST76: MountingHole; Stabilizer_Cherry_MX_6.25u
